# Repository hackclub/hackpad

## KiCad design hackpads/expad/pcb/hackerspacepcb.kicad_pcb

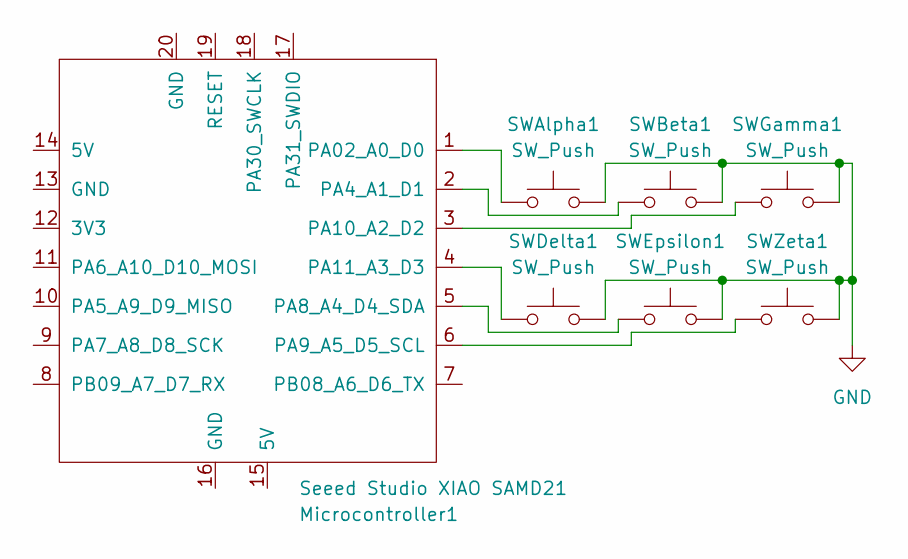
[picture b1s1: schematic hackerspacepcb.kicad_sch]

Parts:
Microcontroller1: Seeed Studio XIAO SAMD21; XIAO-Generic-Thruhole-14P-2.54-21X17.8MM
SWAlpha1: SW_Push; SW_Cherry_MX_1.00u_PCB
SWBeta1: SW_Push; SW_Cherry_MX_1.00u_PCB
SWDelta1: SW_Push; SW_Cherry_MX_1.00u_PCB
SWEpsilon1: SW_Push; SW_Cherry_MX_1.00u_PCB
SWGamma1: SW_Push; SW_Cherry_MX_1.00u_PCB
SWZeta1: SW_Push; SW_Cherry_MX_1.00u_PCB

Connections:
GND: SWAlpha1.2, SWBeta1.2, SWDelta1.2, SWEpsilon1.2, SWGamma1.2, SWZeta1.2
unnamed: Microcontroller1.1 (PA02_A0_D0), SWAlpha1.1
unnamed: Microcontroller1.2 (PA4_A1_D1), SWBeta1.1
unnamed: Microcontroller1.5 (PA8_A4_D4_SDA), SWEpsilon1.1
unnamed: Microcontroller1.6 (PA9_A5_D5_SCL), SWZeta1.1
unnamed: Microcontroller1.3 (PA10_A2_D2), SWGamma1.1
unnamed: Microcontroller1.4 (PA11_A3_D3), SWDelta1.1

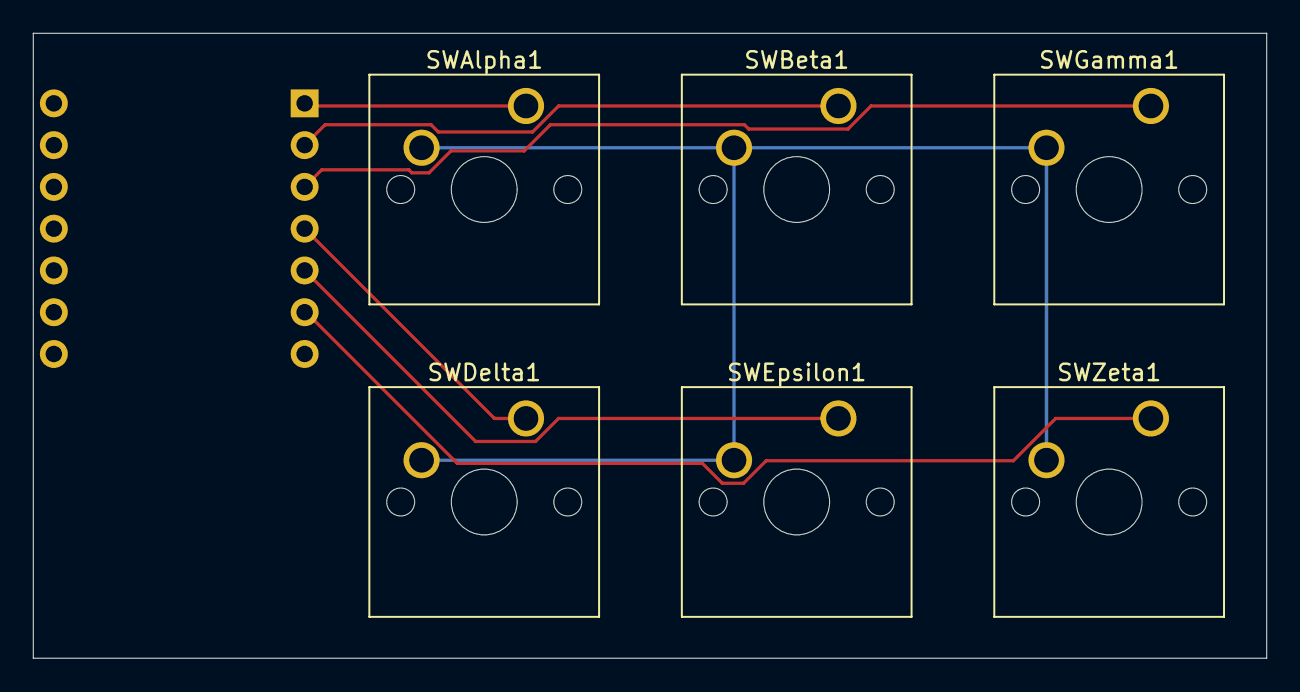
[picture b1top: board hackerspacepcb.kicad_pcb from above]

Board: 2 copper layers, 75.0 x 38.0 mm, 7 parts (1 on the bottom side), 7 nets.

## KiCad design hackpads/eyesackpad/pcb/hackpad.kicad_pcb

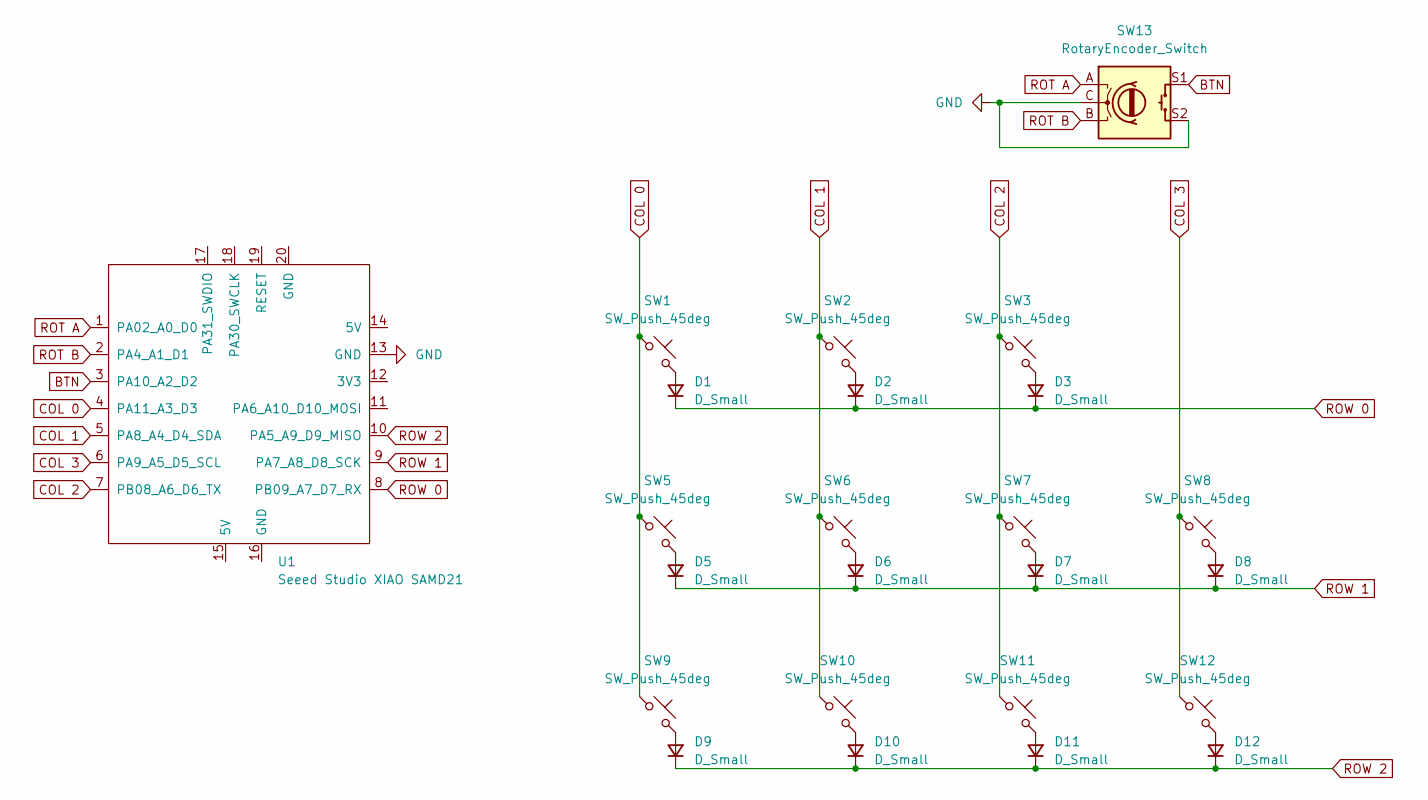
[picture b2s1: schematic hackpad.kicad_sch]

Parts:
D1, D2, D3, D5, D6, D7, D8, D9, D10, D11, D12: D_Small; D_SOD-123
SW1, SW2, SW3, SW5, SW6, SW7, SW8, SW9, SW10, SW11, SW12: SW_Push_45deg; SW_Cherry_MX_1.00u_PCB
SW13: RotaryEncoder_Switch; RotaryEncoder_Alps_EC11E-Switch_Vertical_H20mm_CircularMoun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
U1: Seeed Studio XIAO SAMD21; XIAO-Generic-Thruhole-14P-2.54-21X17.8MM

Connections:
BTN: SW13.S1, U1.3 (PA10_A2_D2)
COL 0: SW1.1, SW5.1, SW9.1, U1.4 (PA11_A3_D3)
COL 1: SW2.1, SW6.1, SW10.1, U1.5 (PA8_A4_D4_SDA)
COL 2: SW3.1, SW7.1, SW11.1, U1.7 (PB08_A6_D6_TX)
COL 3: SW8.1, SW12.1, U1.6 (PA9_A5_D5_SCL)
GND: SW13.C, SW13.S2, U1.13 (GND)
unnamed: D1.2 (A), SW1.2
unnamed: D2.2 (A), SW2.2
unnamed: D3.2 (A), SW3.2
unnamed: D5.2 (A), SW5.2
unnamed: D6.2 (A), SW6.2
unnamed: D7.2 (A), SW7.2
unnamed: D8.2 (A), SW8.2
unnamed: D9.2 (A), SW9.2
unnamed: D10.2 (A), SW10.2
unnamed: D11.2 (A), SW11.2
unnamed: D12.2 (A), SW12.2
ROT A: SW13.A, U1.1 (PA02_A0_D0)
ROT B: SW13.B, U1.2 (PA4_A1_D1)
ROW 0: D1.1 (K), D2.1 (K), D3.1 (K), U1.8 (PB09_A7_D7_RX)
ROW 1: D5.1 (K), D6.1 (K), D7.1 (K), D8.1 (K), U1.9 (PA7_A8_D8_SCK)
ROW 2: D9.1 (K), D10.1 (K), D11.1 (K), D12.1 (K), U1.10 (PA5_A9_D9_MISO)

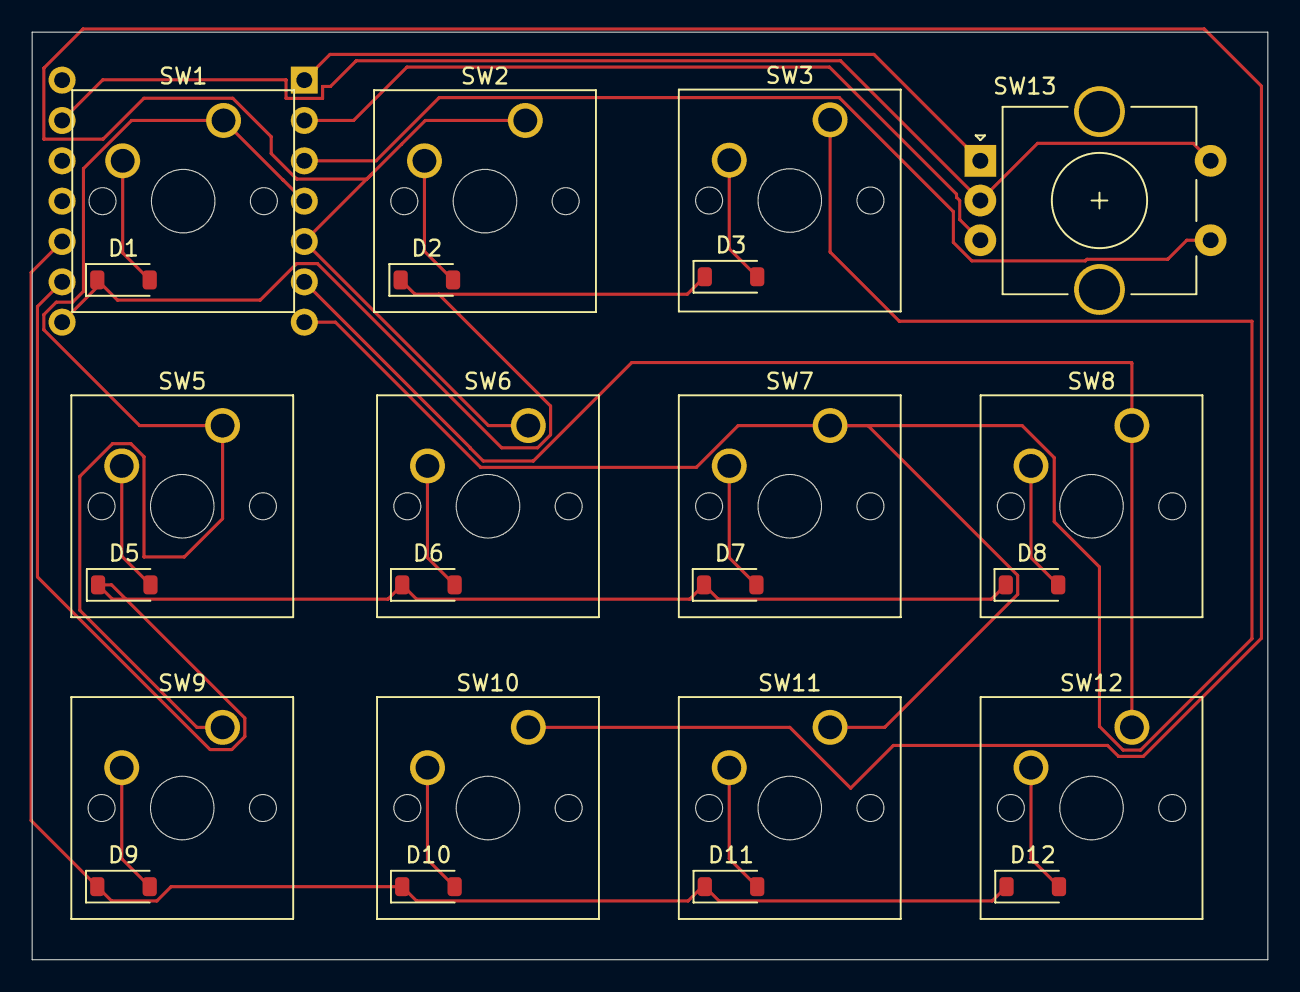
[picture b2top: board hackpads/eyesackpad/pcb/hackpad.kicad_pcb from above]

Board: 2 copper layers, 77.8 x 58.4 mm, 24 parts (1 on the bottom side), 22 nets.

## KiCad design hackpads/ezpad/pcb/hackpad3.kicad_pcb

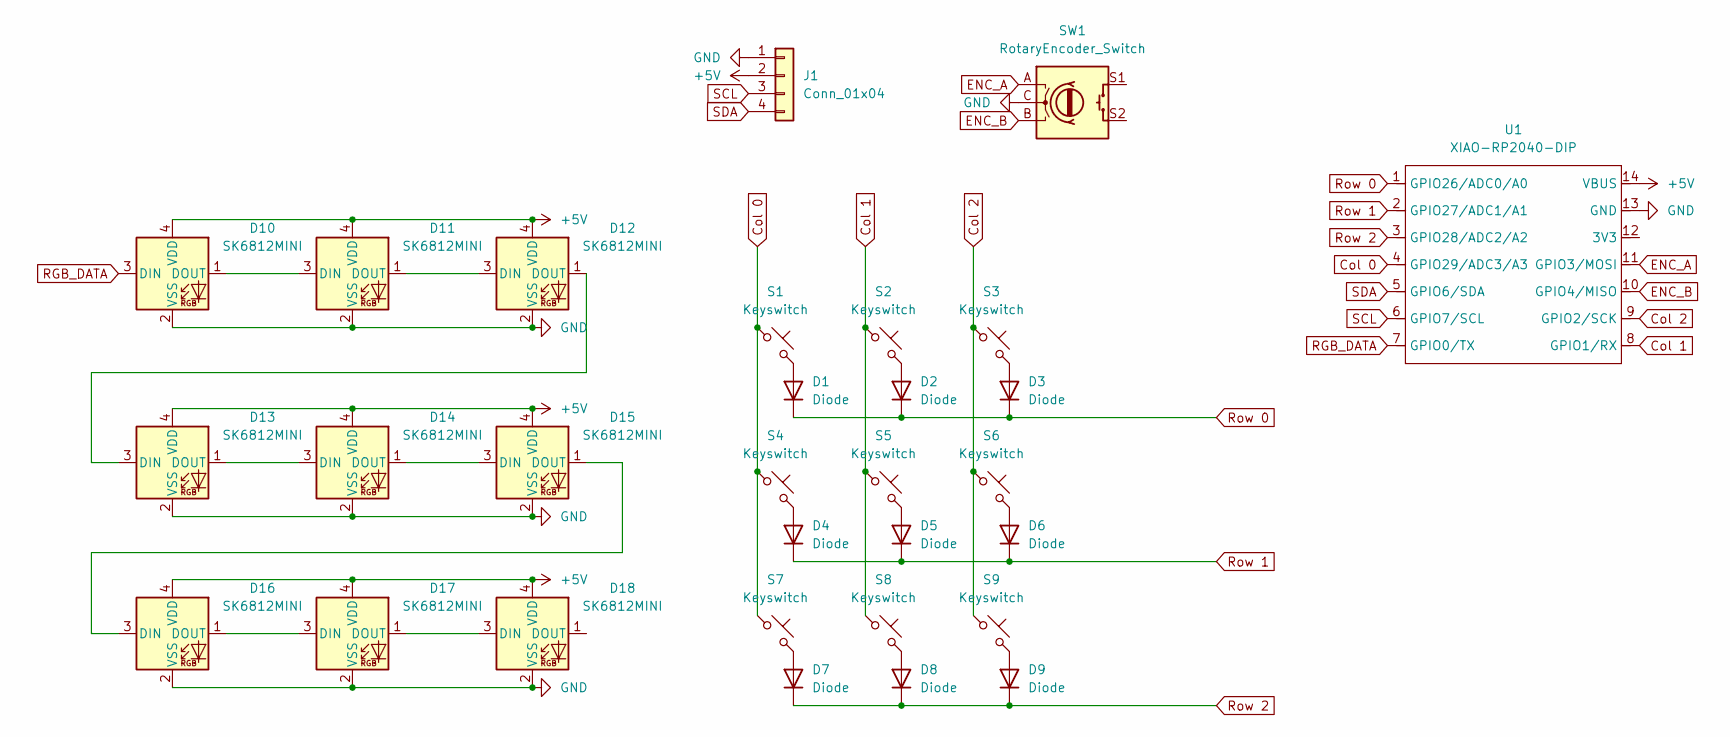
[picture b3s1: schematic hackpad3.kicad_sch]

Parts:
D1, D2, D3, D4, D5, D6, D7, D8, D9: Diode; Diode_DO-35
D10, D11, D12, D13, D14, D15, D16, D17, D18: SK6812MINI; LED_SK6812MINI
J1: Conn_01x04; SSD1306-0.91-OLED-4pin-128x32
S1, S2, S3, S4, S5, S6, S7, S8, S9: Keyswitch; Hotswap_MX_1.00u
SW1: RotaryEncoder_Switch; RotaryEncoder_Alps_EC11E-Switch_Vertical_H20mm
U1: XIAO-RP2040-DIP

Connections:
+5V: D10.4 (VDD), D11.4 (VDD), D12.4 (VDD), D13.4 (VDD), D14.4 (VDD), D15.4 (VDD), D16.4 (VDD), D17.4 (VDD), D18.4 (VDD), J1.2, U1.14 (VBUS)
Col 0: S1.1, S4.1, S7.1, U1.4 (GPIO29/ADC3/A3)
Col 1: S2.1, S5.1, S8.1, U1.8 (GPIO1/RX)
Col 2: S3.1, S6.1, S9.1, U1.9 (GPIO2/SCK)
ENC_A: SW1.A, U1.11 (GPIO3/MOSI)
ENC_B: SW1.B, U1.10 (GPIO4/MISO)
GND: D10.2 (VSS), D11.2 (VSS), D12.2 (VSS), D13.2 (VSS), D14.2 (VSS), D15.2 (VSS), D16.2 (VSS), D17.2 (VSS), D18.2 (VSS), J1.1, SW1.C, U1.13 (GND)
unnamed: D1.2 (A), S1.2
unnamed: D2.2 (A), S2.2
unnamed: D3.2 (A), S3.2
unnamed: D4.2 (A), S4.2
unnamed: D5.2 (A), S5.2
unnamed: D6.2 (A), S6.2
unnamed: D7.2 (A), S7.2
unnamed: D8.2 (A), S8.2
unnamed: D9.2 (A), S9.2
unnamed: D10.1 (DOUT), D11.3 (DIN)
unnamed: D11.1 (DOUT), D12.3 (DIN)
unnamed: D12.1 (DOUT), D13.3 (DIN)
unnamed: D13.1 (DOUT), D14.3 (DIN)
unnamed: D14.1 (DOUT), D15.3 (DIN)
unnamed: D15.1 (DOUT), D16.3 (DIN)
unnamed: D16.1 (DOUT), D17.3 (DIN)
unnamed: D17.1 (DOUT), D18.3 (DIN)
RGB_DATA: D10.3 (DIN), U1.7 (GPIO0/TX)
Row 0: D1.1 (K), D2.1 (K), D3.1 (K), U1.1 (GPIO26/ADC0/A0)
Row 1: D4.1 (K), D5.1 (K), D6.1 (K), U1.2 (GPIO27/ADC1/A1)
Row 2: D7.1 (K), D8.1 (K), D9.1 (K), U1.3 (GPIO28/ADC2/A2)
SCL: J1.3, U1.6 (GPIO7/SCL)
SDA: J1.4, U1.5 (GPIO6/SDA)

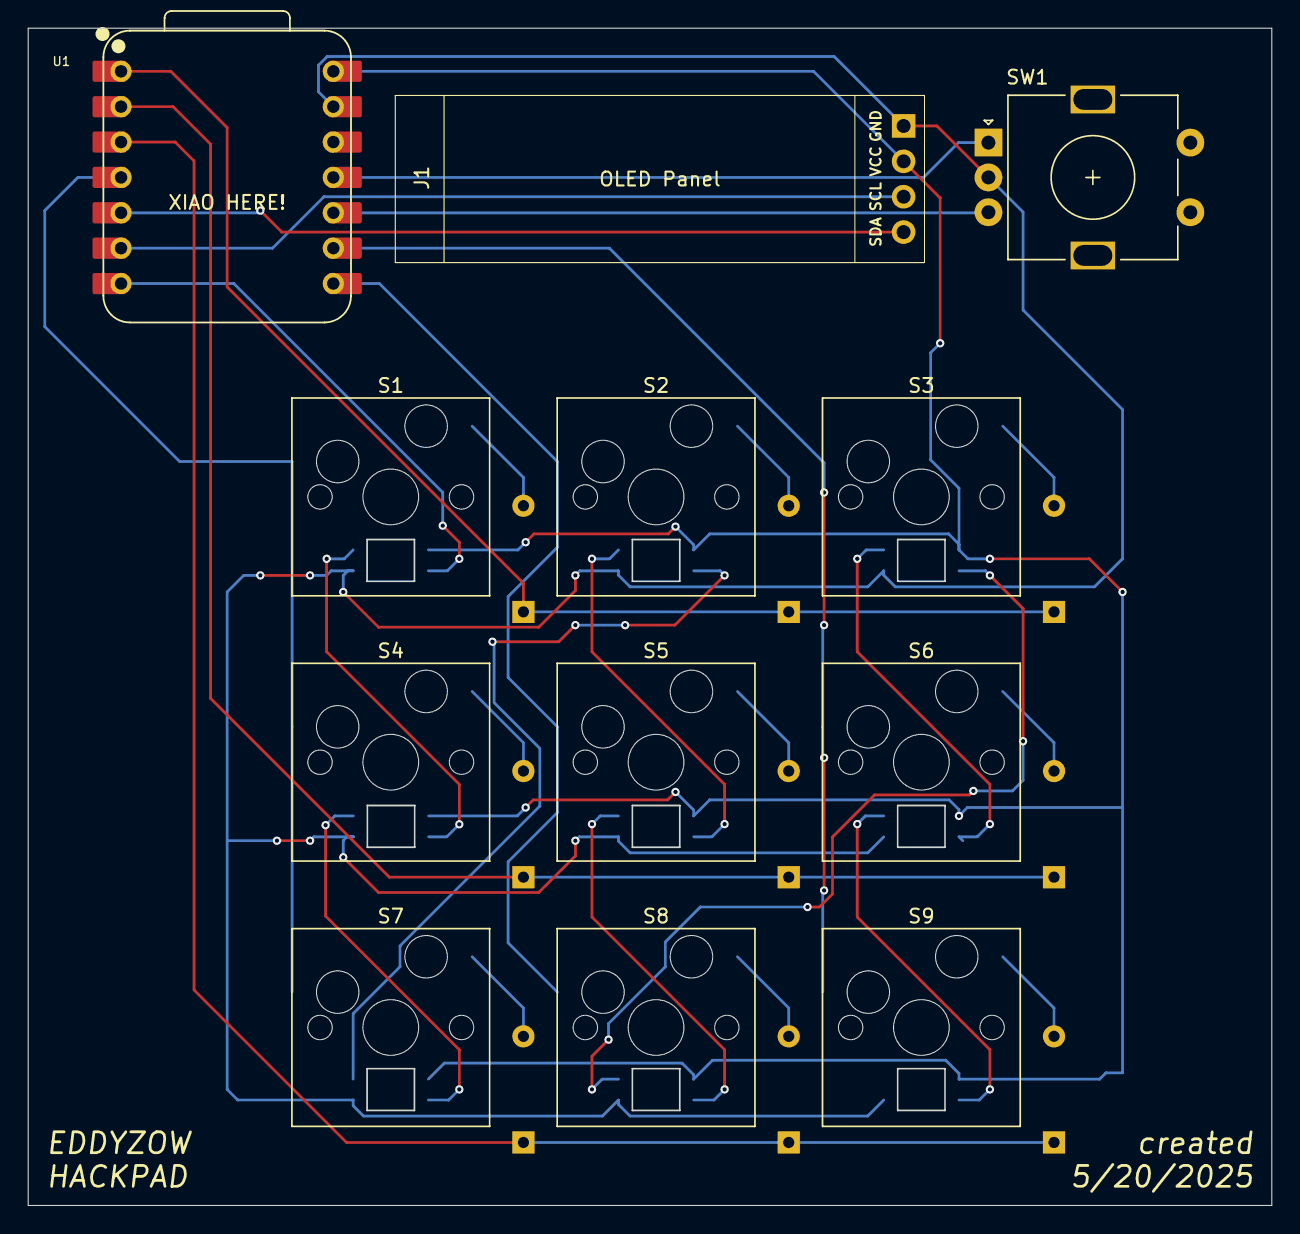
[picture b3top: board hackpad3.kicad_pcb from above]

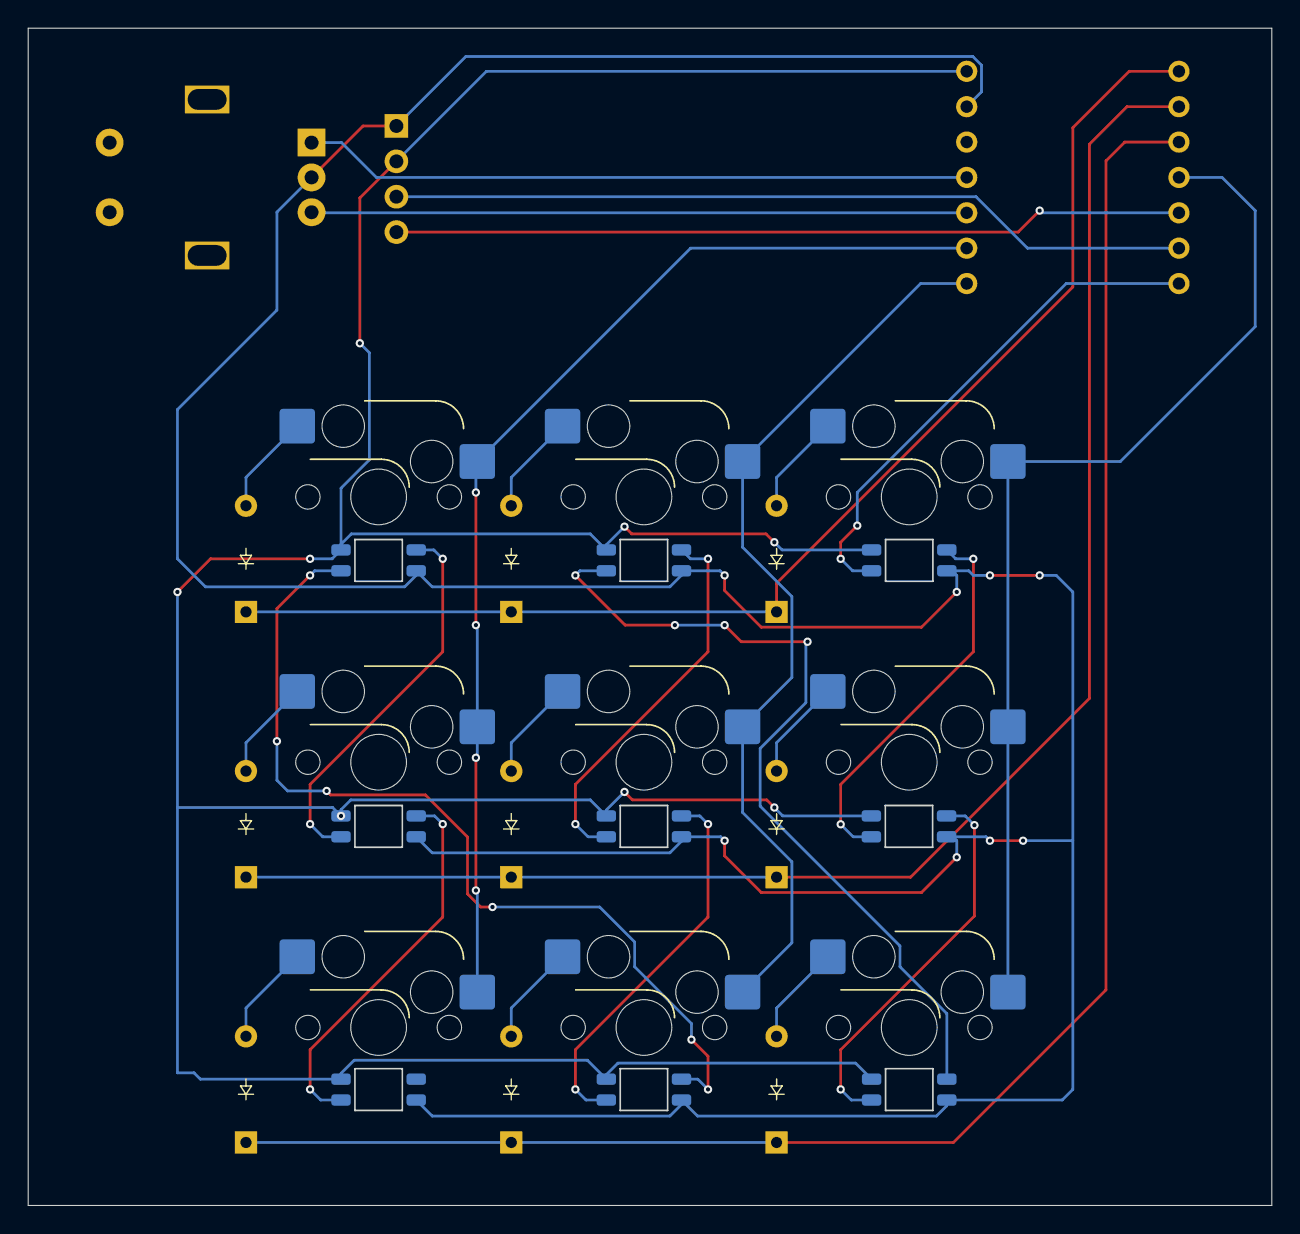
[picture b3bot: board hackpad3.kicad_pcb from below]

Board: 2 copper layers, 89.3 x 84.5 mm, 30 parts (18 on the bottom side), 30 nets.

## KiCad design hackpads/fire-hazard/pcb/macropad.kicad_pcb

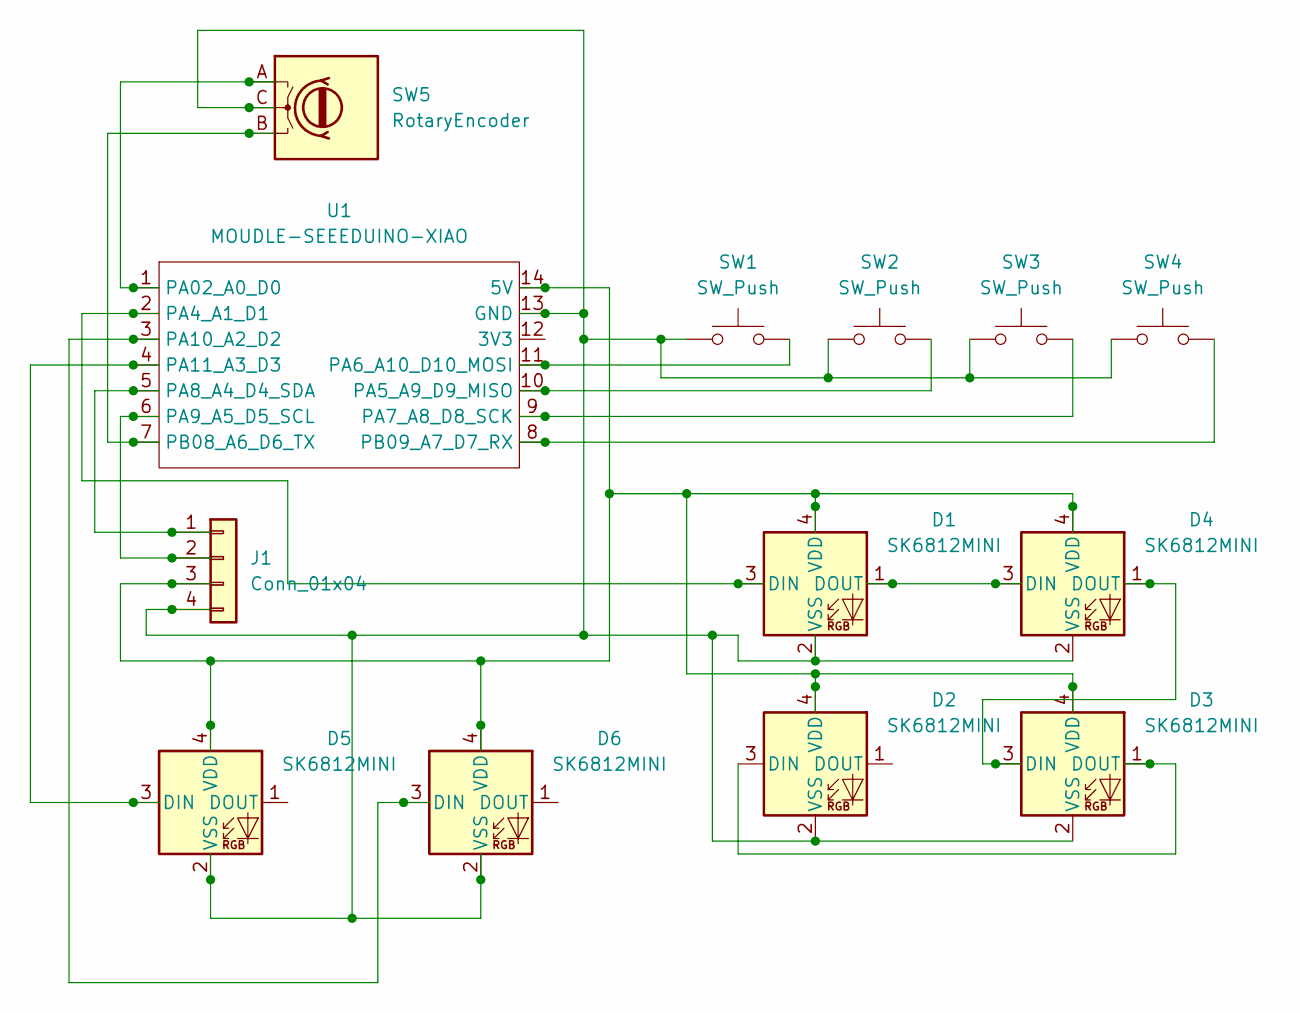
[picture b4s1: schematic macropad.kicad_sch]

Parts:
D1, D2, D3, D4, D5, D6: SK6812MINI; LED_SK6812MINI_PLCC4_3.5x3.5mm_P1.75mm
J1: Conn_01x04; MODULE_DM-OLED096-636
SW1, SW2, SW3, SW4: SW_Push; SW_Cherry_MX_1.00u_PCB
SW5: RotaryEncoder; RotaryEncoder_Alps_EC11E-Switch_Vertical_H20mm
U1: MOUDLE-SEEEDUINO-XIAO; XIAO-RP2040-SMD

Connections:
unnamed: D1.3 (DIN), U1.2 (PA4_A1_D1)
unnamed: D1.1 (DOUT), D4.3 (DIN)
unnamed: D1.4 (VDD), D2.4 (VDD), D3.4 (VDD), D4.4 (VDD), D5.4 (VDD), D6.4 (VDD), J1.3, U1.14 (5V)
unnamed: D1.2 (VSS), D2.2 (VSS), D3.2 (VSS), D4.2 (VSS), D5.2 (VSS), D6.2 (VSS), J1.4, SW1.1, SW2.1, SW3.1, SW4.1, SW5.C, U1.13 (GND)
unnamed: D2.3 (DIN), D3.1 (DOUT)
unnamed: D3.3 (DIN), D4.1 (DOUT)
unnamed: D5.3 (DIN), U1.4 (PA11_A3_D3)
unnamed: D6.3 (DIN), U1.3 (PA10_A2_D2)
unnamed: J1.1, U1.5 (PA8_A4_D4_SDA)
unnamed: J1.2, U1.6 (PA9_A5_D5_SCL)
unnamed: SW5.A, U1.1 (PA02_A0_D0)
unnamed: SW2.2, U1.10 (PA5_A9_D9_MISO)
unnamed: SW1.2, U1.11 (PA6_A10_D10_MOSI)
unnamed: SW3.2, U1.9 (PA7_A8_D8_SCK)
unnamed: SW5.B, U1.7 (PB08_A6_D6_TX)
unnamed: SW4.2, U1.8 (PB09_A7_D7_RX)

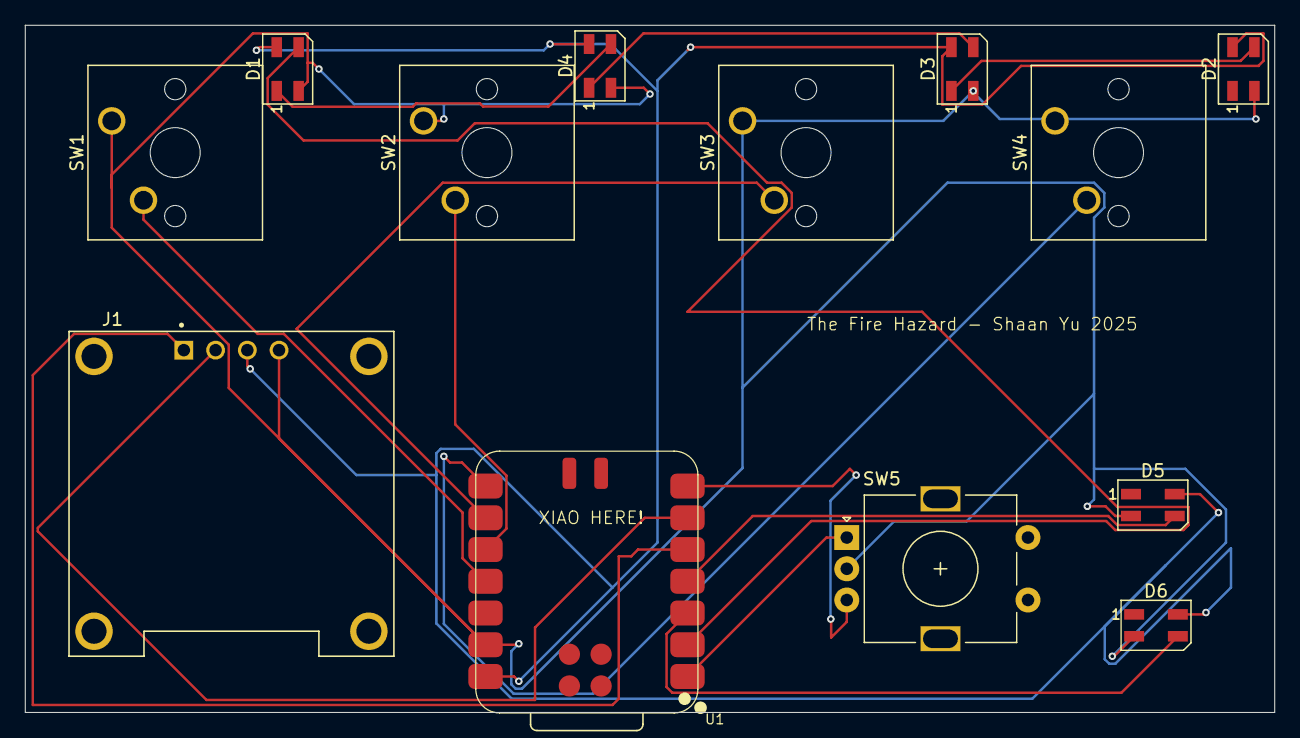
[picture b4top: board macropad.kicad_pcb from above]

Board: 2 copper layers, 100.0 x 55.0 mm, 13 parts (0 on the bottom side), 16 nets.

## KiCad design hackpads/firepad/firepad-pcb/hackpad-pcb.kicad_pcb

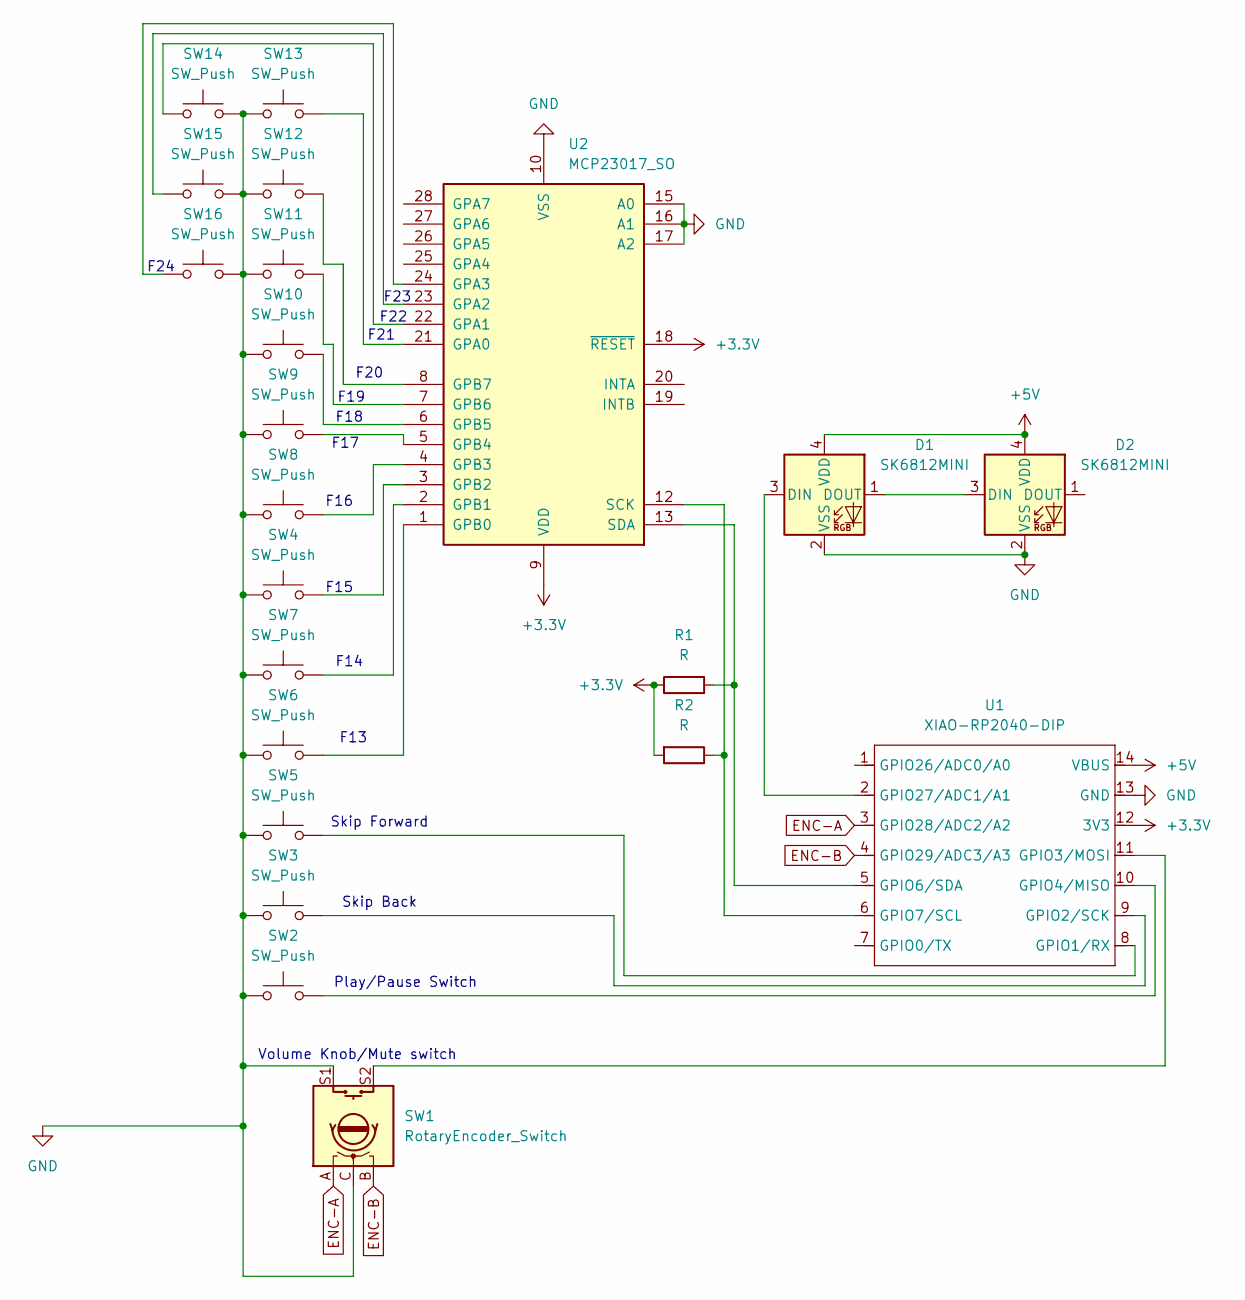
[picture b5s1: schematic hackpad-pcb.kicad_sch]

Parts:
D1, D2: SK6812MINI; LED_SK6812MINI_PLCC4_3.5x3.5mm_P1.75mm_3D
R1, R2: R; R_Axial_DIN0204_L3.6mm_D1.6mm_P7.62mm_Horizontal
SW1: RotaryEncoder_Switch; RotaryEncoder_Alps_EC11E-Switch_Vertical_H20mm_CircularMoun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
SW2, SW3, SW4, SW5, SW6, SW7, SW8, SW9, SW10, SW11, SW12, SW13, SW14, SW15, SW16: SW_Push; SW_Cherry_MX_1.00u_PCB_3D
U1: XIAO-RP2040-DIP; XIAO-RP2040-DIP-3D
U2: MCP23017_SO; SOIC-28W_7.5x17.9mm_P1.27mm

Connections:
+3.3V: R1.1, R2.2, U1.12 (3V3), U2.9 (VDD), U2.18 (~RESET)
+5V: D1.4 (VDD), D2.4 (VDD), U1.14 (VBUS)
ENC-A: SW1.A, U1.3 (GPIO28/ADC2/A2)
ENC-B: SW1.B, U1.4 (GPIO29/ADC3/A3)
GND: D1.2 (VSS), D2.2 (VSS), SW1.C, SW1.S1, SW2.1, SW3.1, SW4.1, SW5.1, SW6.1, SW7.1, SW8.1, SW9.1, SW10.1, SW11.1, SW12.1, SW13.1, SW14.2, SW15.2, SW16.2, U1.13 (GND), U2.10 (VSS), U2.15 (A0), U2.16 (A1), U2.17 (A2)
unnamed: D1.3 (DIN), U1.2 (GPIO27/ADC1/A1)
unnamed: D1.1 (DOUT), D2.3 (DIN)
unnamed: SW5.2, U1.8 (GPIO1/RX)
unnamed: SW3.2, U1.9 (GPIO2/SCK)
unnamed: SW1.S2, U1.11 (GPIO3/MOSI)
unnamed: SW2.2, U1.10 (GPIO4/MISO)
unnamed: R1.2, U1.5 (GPIO6/SDA), U2.13 (SDA)
unnamed: R2.1, U1.6 (GPIO7/SCL), U2.12 (SCK)
unnamed: SW13.2, U2.21 (GPA0)
unnamed: SW14.1, U2.22 (GPA1)
unnamed: SW15.1, U2.23 (GPA2)
unnamed: SW16.1, U2.24 (GPA3)
unnamed: SW6.2, U2.1 (GPB0)
unnamed: SW7.2, U2.2 (GPB1)
unnamed: SW4.2, U2.3 (GPB2)
unnamed: SW8.2, U2.4 (GPB3)
unnamed: SW9.2, U2.5 (GPB4)
unnamed: SW10.2, U2.6 (GPB5)
unnamed: SW11.2, U2.7 (GPB6)
unnamed: SW12.2, U2.8 (GPB7)

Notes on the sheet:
F15
F21
F14
Skip Forward
F13
F19
Volume Knob/Mute switch
F23
F24
F22
F17
F16
Play/Pause Switch
F18
Skip Back
F20

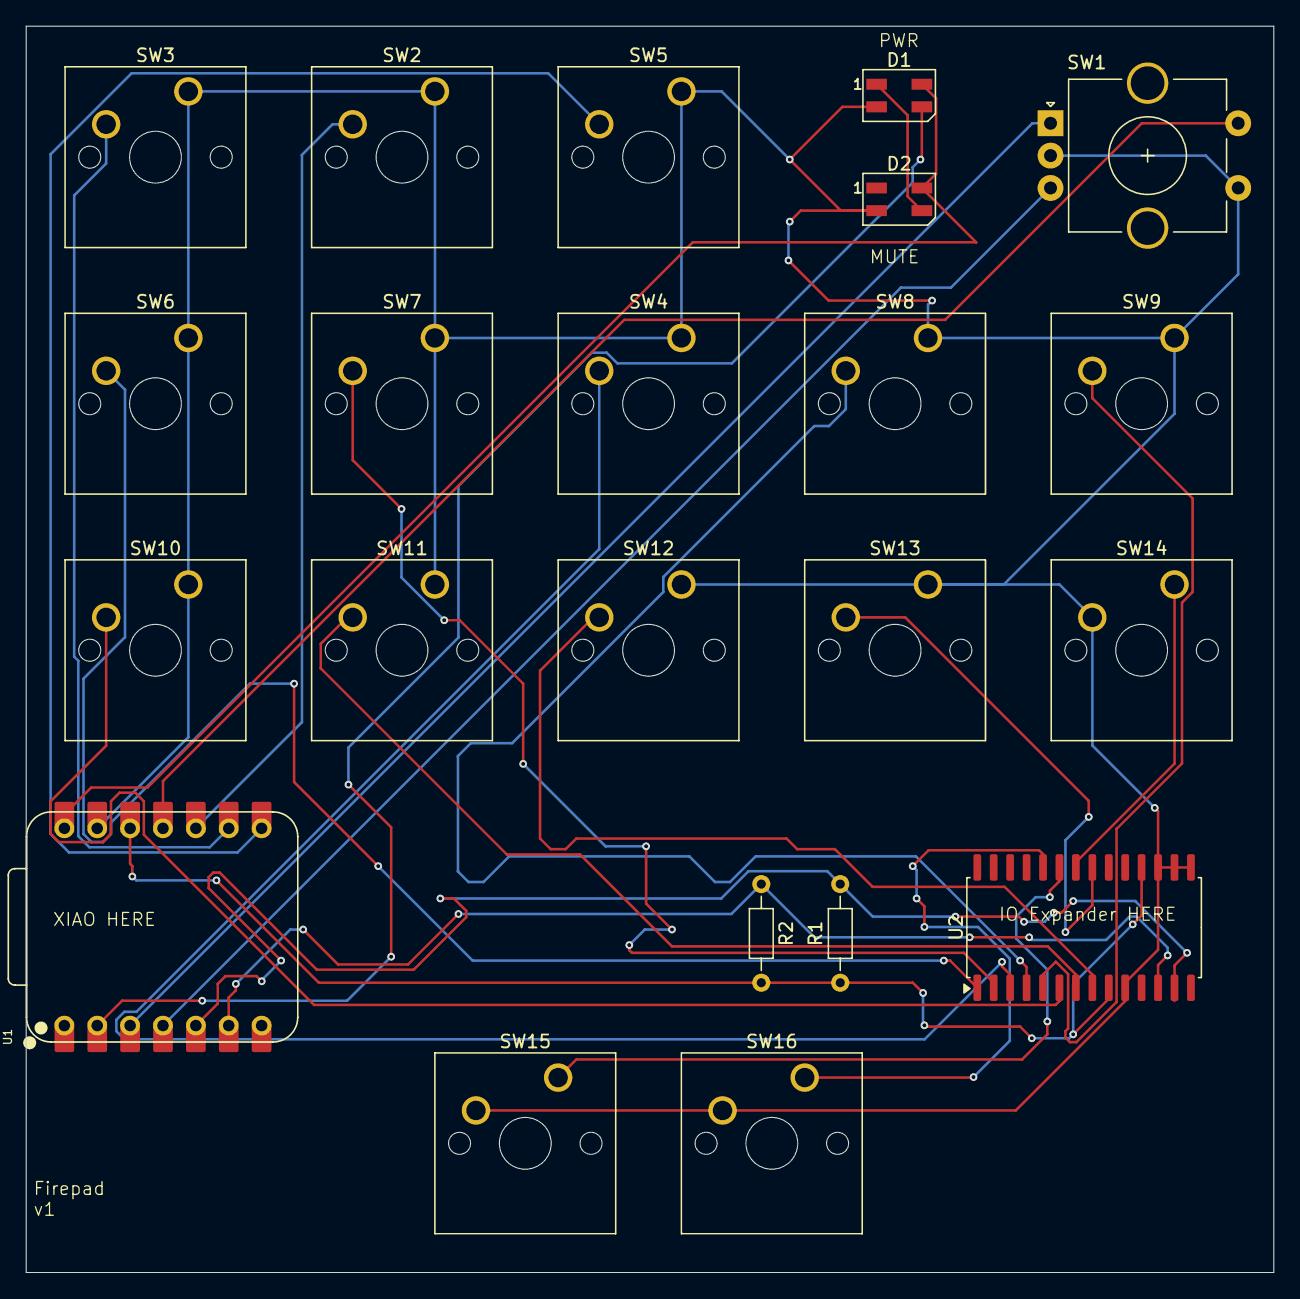
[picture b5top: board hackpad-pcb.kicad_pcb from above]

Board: 2 copper layers, 96.4 x 96.3 mm, 22 parts (0 on the bottom side), 25 nets.

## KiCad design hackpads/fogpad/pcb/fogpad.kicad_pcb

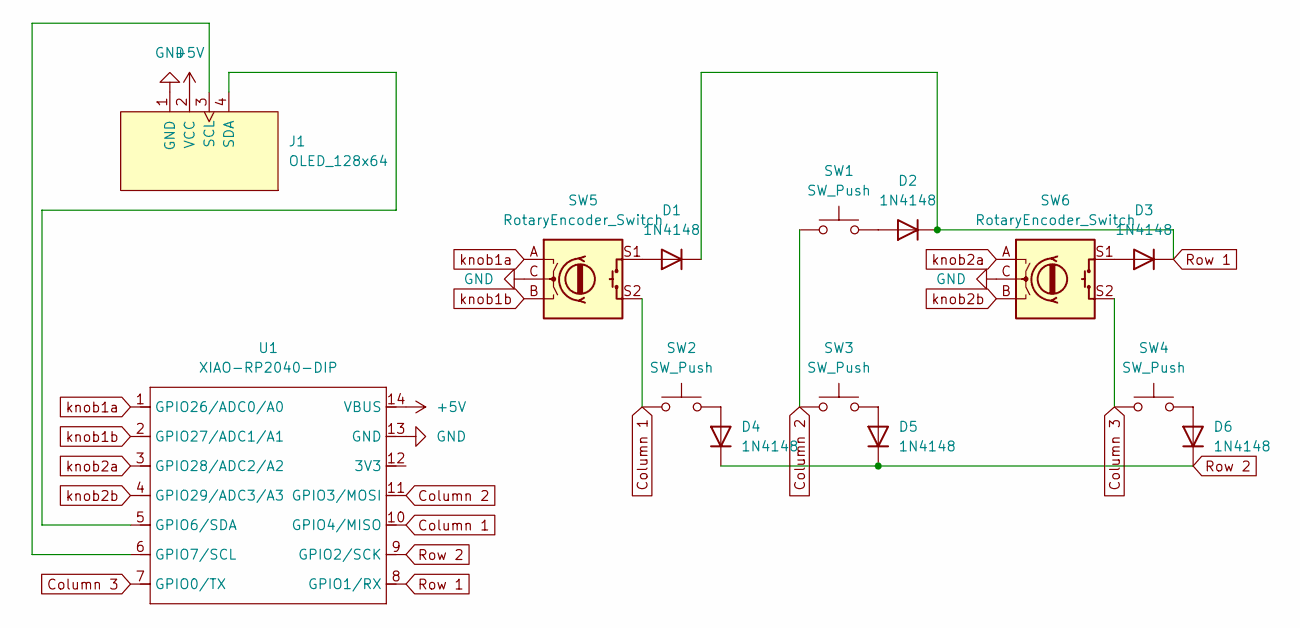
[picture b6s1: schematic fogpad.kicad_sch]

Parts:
D1, D2, D3, D4, D5, D6: 1N4148; D_DO-35_SOD27_P7.62mm_Horizontal
J1: OLED_128x64
SW1, SW2, SW3, SW4: SW_Push; SW_Cherry_MX_1.00u_PCB
SW5, SW6: RotaryEncoder_Switch; RotaryEncoder_Alps_EC11E-Switch_Vertical_H20mm
U1: XIAO-RP2040-DIP

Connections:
+5V: J1.2 (VCC), U1.14 (VBUS)
Column 1: SW2.1, SW5.S2, U1.10 (GPIO4/MISO)
Column 2: SW1.1, SW3.1, U1.11 (GPIO3/MOSI)
Column 3: SW4.1, SW6.S2, U1.7 (GPIO0/TX)
GND: J1.1 (GND), SW5.C, SW6.C, U1.13 (GND)
unnamed: D1.2 (A), SW5.S1
unnamed: D2.2 (A), SW1.2
unnamed: D3.2 (A), SW6.S1
unnamed: D4.2 (A), SW2.2
unnamed: D5.2 (A), SW3.2
unnamed: D6.2 (A), SW4.2
unnamed: J1.3 (SCL), U1.6 (GPIO7/SCL)
unnamed: J1.4 (SDA), U1.5 (GPIO6/SDA)
Row 1: D1.1 (K), D2.1 (K), D3.1 (K), U1.8 (GPIO1/RX)
Row 2: D4.1 (K), D5.1 (K), D6.1 (K), U1.9 (GPIO2/SCK)
knob1a: SW5.A, U1.1 (GPIO26/ADC0/A0)
knob1b: SW5.B, U1.2 (GPIO27/ADC1/A1)
knob2a: SW6.A, U1.3 (GPIO28/ADC2/A2)
knob2b: SW6.B, U1.4 (GPIO29/ADC3/A3)

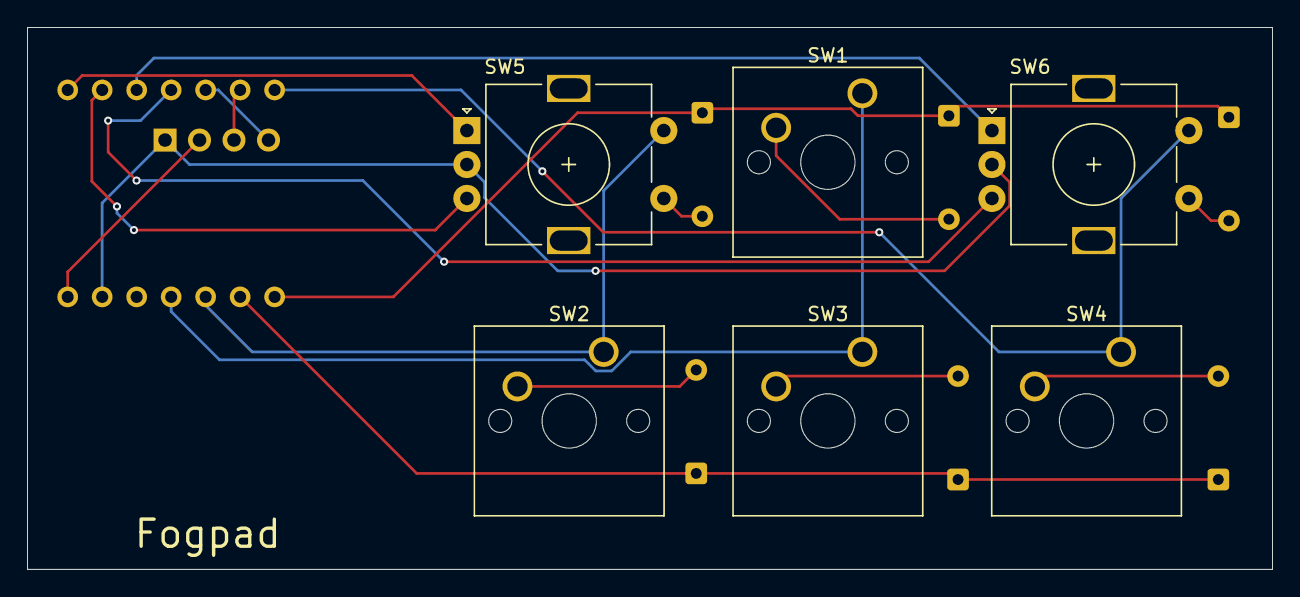
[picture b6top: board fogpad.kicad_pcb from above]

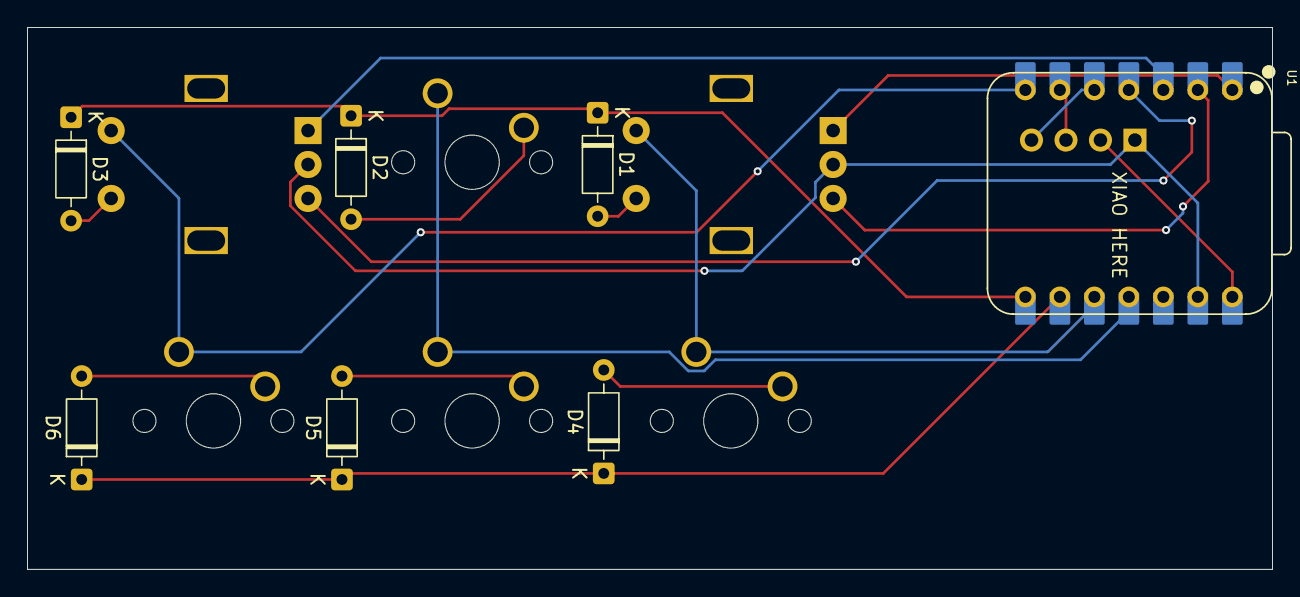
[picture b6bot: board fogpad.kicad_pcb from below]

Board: 2 copper layers, 91.7 x 39.9 mm, 14 parts (7 on the bottom side), 19 nets.

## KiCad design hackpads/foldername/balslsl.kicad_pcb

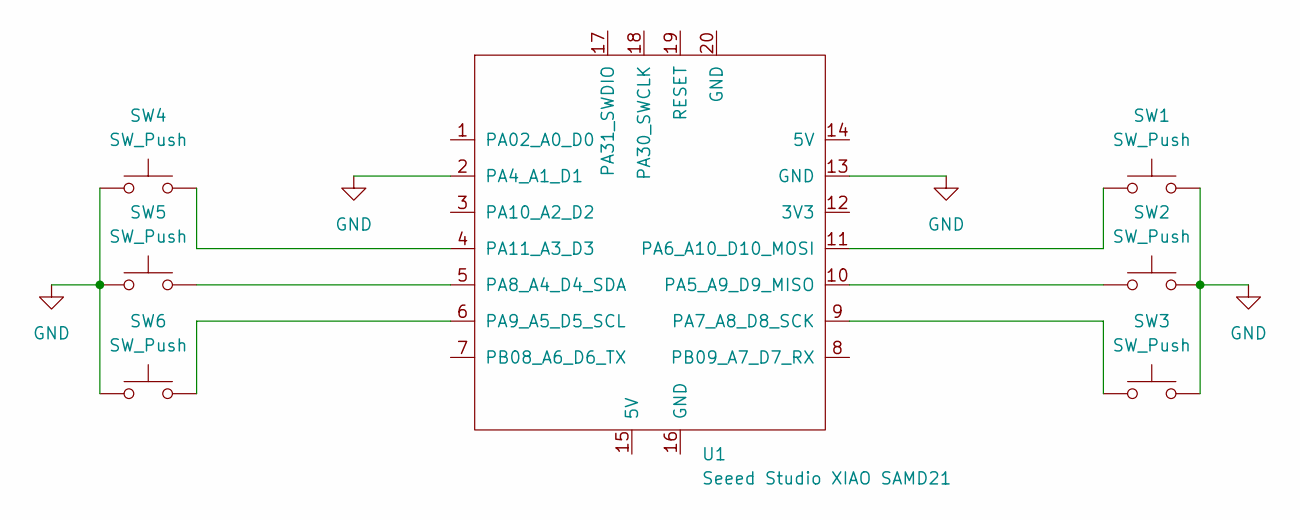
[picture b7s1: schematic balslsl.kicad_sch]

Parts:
SW1, SW2, SW3, SW4, SW5, SW6: SW_Push; SW_Cherry_MX_1.00u_PCB
U1: Seeed Studio XIAO SAMD21; XIAO-Generic-Thruhole-14P-2.54-21X17.8MM

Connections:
GND: SW1.2, SW2.2, SW3.2, SW4.2, SW5.2, SW6.2, U1.2 (PA4_A1_D1), U1.13 (GND)
unnamed: SW2.1, U1.10 (PA5_A9_D9_MISO)
unnamed: SW1.1, U1.11 (PA6_A10_D10_MOSI)
unnamed: SW3.1, U1.9 (PA7_A8_D8_SCK)
unnamed: SW5.1, U1.5 (PA8_A4_D4_SDA)
unnamed: SW6.1, U1.6 (PA9_A5_D5_SCL)
unnamed: SW4.1, U1.4 (PA11_A3_D3)
